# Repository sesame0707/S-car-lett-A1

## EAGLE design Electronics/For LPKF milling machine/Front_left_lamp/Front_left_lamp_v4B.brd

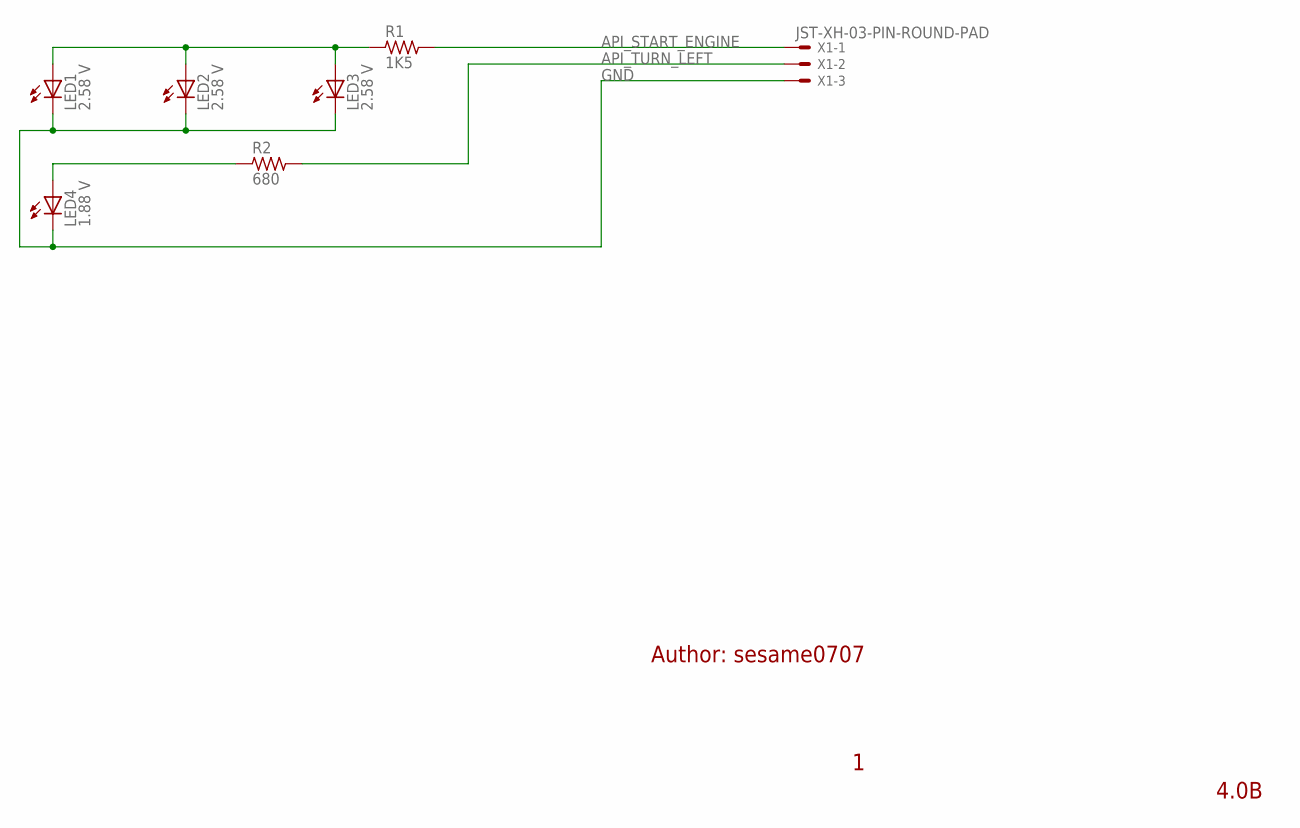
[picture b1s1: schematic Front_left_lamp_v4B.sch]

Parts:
LED1, LED2, LED3: 2.58 V; LED5MM
LED4: 1.88 V; LED5MM
R1: 1K5; R1206
R2: 680; R1206
X1: JST-XH-03-PIN-ROUND-PAD; JST-XH-03-PACKAGE-ROUND-PAD

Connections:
API_START_ENGINE: LED1.A, LED2.A, LED3.A, R1.1
API_TURN_LEFT: R2.2, X1.2
GND: LED1.K (C), LED2.K (C), LED3.K (C), LED4.K (C), X1.3
unnamed: R1.2, X1.1
unnamed: LED4.A, R2.1

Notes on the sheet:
Author: sesame0707
4.0B

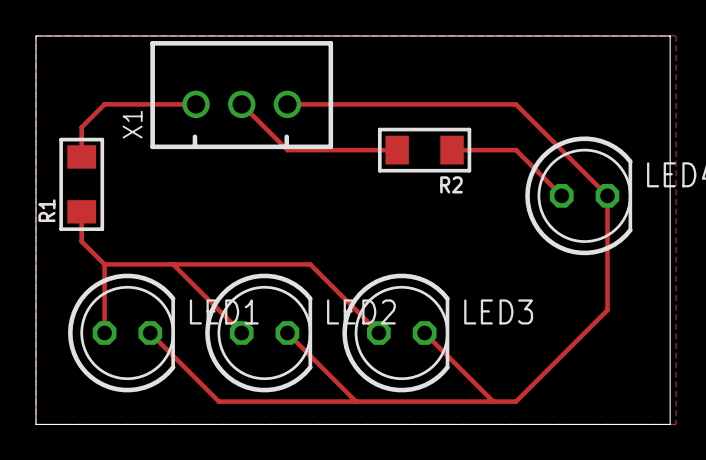
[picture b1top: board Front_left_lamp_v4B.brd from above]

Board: 2 copper layers, 35.2 x 21.6 mm, 7 parts (0 on the bottom side), 5 nets.

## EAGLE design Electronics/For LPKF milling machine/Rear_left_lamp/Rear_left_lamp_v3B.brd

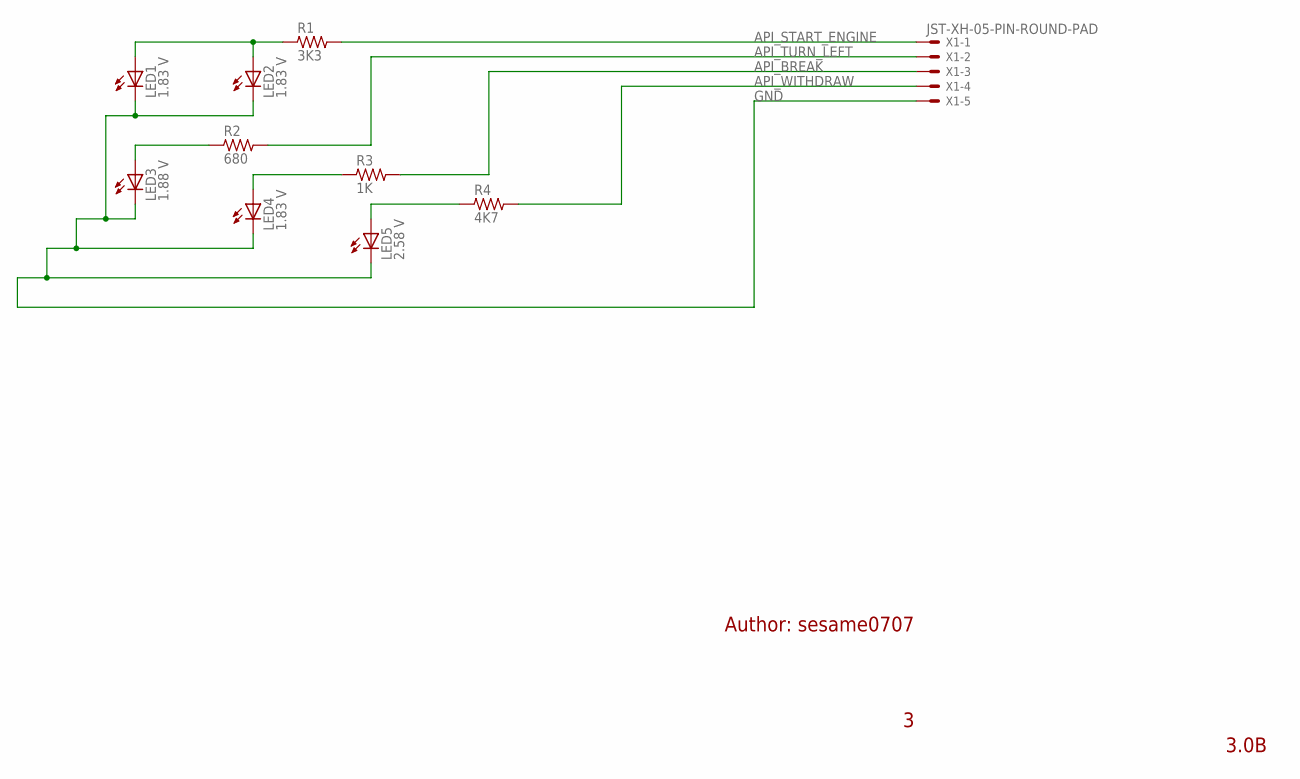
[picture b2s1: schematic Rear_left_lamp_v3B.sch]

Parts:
LED1, LED2, LED4: 1.83 V; LED5MM
LED3: 1.88 V; LED5MM
LED5: 2.58 V; LED5MM
R1: 3K3; R1206
R2: 680; R1206
R3: 1K; R1206
R4: 4K7; R1206
X1: JST-XH-05-PIN-ROUND-PAD; JST-XH-05-PACKAGE-ROUND-PAD

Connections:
API_BREAK: R3.2, X1.3
API_START_ENGINE: LED1.A, LED2.A, R1.1
API_TURN_LEFT: R2.2, X1.2
API_WITHDRAW: R4.2, X1.4
GND: LED1.K (C), LED2.K (C), LED3.K (C), LED4.K (C), LED5.K (C), X1.5
unnamed: LED3.A, R2.1
unnamed: R1.2, X1.1
unnamed: LED4.A, R3.1
unnamed: LED5.A, R4.1

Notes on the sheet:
Author: sesame0707
3.0B

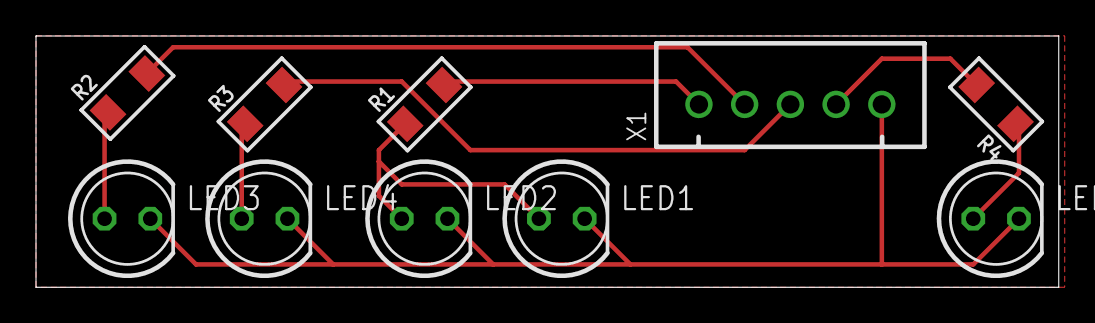
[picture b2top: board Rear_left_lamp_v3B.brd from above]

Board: 2 copper layers, 56.8 x 14.0 mm, 10 parts (0 on the bottom side), 9 nets.

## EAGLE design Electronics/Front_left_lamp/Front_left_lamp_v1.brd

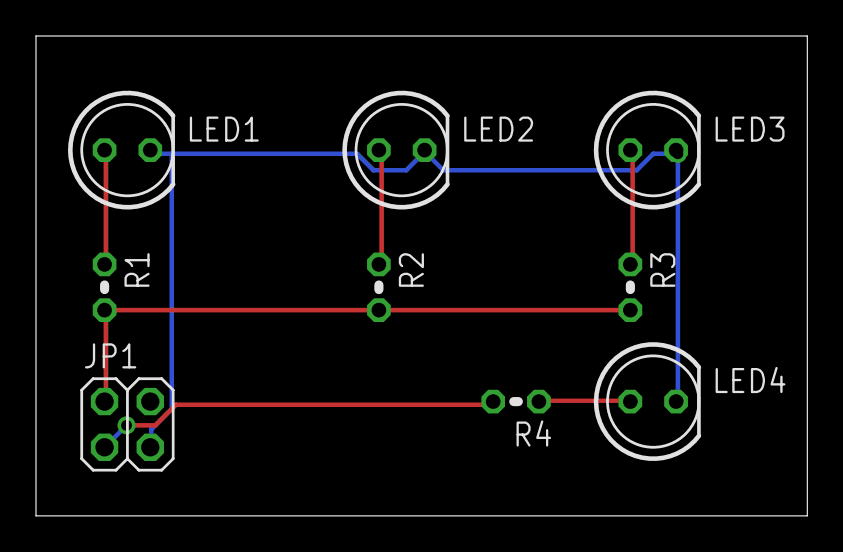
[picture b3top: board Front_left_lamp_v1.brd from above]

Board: 2 copper layers, 42.9 x 26.7 mm, 9 parts (0 on the bottom side), 7 nets.

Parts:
JP1: 2X2; 2X02
LED1, LED2, LED3, LED4: 2V2; LED5MM
R1, R2, R3, R4: 220; 0204V

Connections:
unnamed: LED1.A, R1.1
unnamed: LED2.A, R2.1
unnamed: LED3.A, R3.1
unnamed: LED4.A, R4.1
unnamed: JP1.2, R1.2, R2.2, R3.2
unnamed: JP1.1, R4.2
unnamed: JP1.3, LED1.K, LED2.K, LED3.K, LED4.K

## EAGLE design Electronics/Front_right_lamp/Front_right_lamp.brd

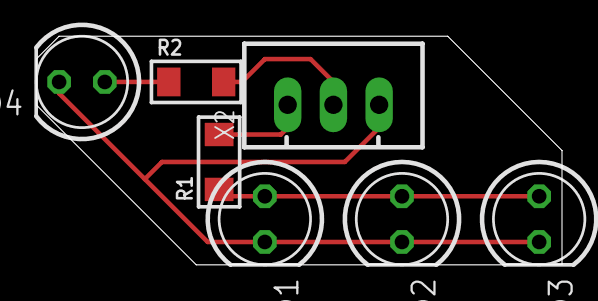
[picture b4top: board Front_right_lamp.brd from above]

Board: 2 copper layers, 29.2 x 12.7 mm, 7 parts (0 on the bottom side), 5 nets.

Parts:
LED1, LED2, LED3: White; LED5MM
LED4: Yellow; LED5MM
R1: 1K5; R1206
R2: 680; R1206
X2: JST-XH-03-PIN-LONG-PAD; JST-XH-03-PACKAGE-LONG-PAD

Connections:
API_START_ENGINE: LED1.A, LED2.A, LED3.A, R1.1
API_TURN_RIGHT: R2.2, X2.2
GND: LED1.K, LED2.K, LED3.K, LED4.K, X2.3
unnamed: LED4.A, R2.1
unnamed: R1.2, X2.1

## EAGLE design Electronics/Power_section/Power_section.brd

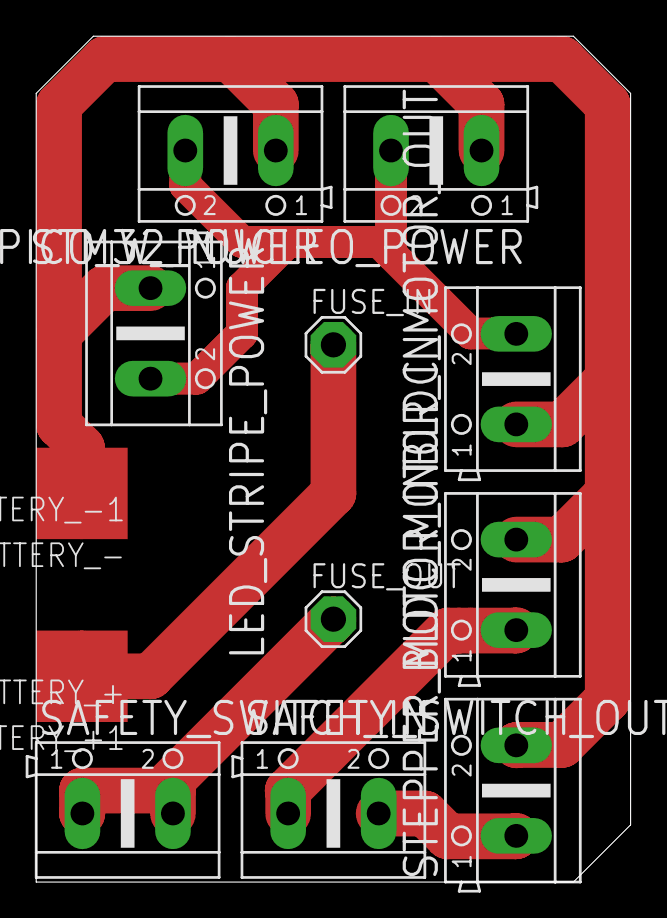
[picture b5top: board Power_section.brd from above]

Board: 2 copper layers, 33.0 x 47.0 mm, 14 parts (0 on the bottom side), 6 nets.

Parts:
BATTERY_+, BATTERY_+1: WIREPADSMD2,54-5,08; SMD2,54-5,08
BATTERY_-, BATTERY_-1: WIREPADSMD2,54-5,08; SMD2,54-5,08
BLDC_MOTOR_IN: AK500/2
BLDC_MOTOR_OUT: AK500/2
FUSE_IN: SE14
FUSE_OUT: SE14
LED_STRIPE_POWER: AK500/2
RPI_PICO_W_POWER: AK500/2
SAFETY_SWITCH_IN: AK500/2
SAFETY_SWITCH_OUT: AK500/2
STEPPER_MOTOR_IN: AK500/2
STM32_NUCLEO_POWER: AK500/2

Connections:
5V: BLDC_MOTOR_OUT.2, LED_STRIPE_POWER.2, RPI_PICO_W_POWER.2, STM32_NUCLEO_POWER.2
12V: FUSE_OUT.MP, SAFETY_SWITCH_IN.1, SAFETY_SWITCH_IN.2
BLDC_MOTOR: BLDC_MOTOR_IN.1, SAFETY_SWITCH_OUT.1
GND: BATTERY_-.1, BATTERY_-1.1, BLDC_MOTOR_IN.2, BLDC_MOTOR_OUT.1, LED_STRIPE_POWER.1, RPI_PICO_W_POWER.1, STEPPER_MOTOR_IN.2, STM32_NUCLEO_POWER.1
unnamed: BATTERY_+.1, BATTERY_+1.1, FUSE_IN.MP
STEPPER_MOTOR: SAFETY_SWITCH_OUT.2, STEPPER_MOTOR_IN.1

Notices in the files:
parts and their libraries:
rc-master-smd: Copyright (C) 2007, Bob Starr
